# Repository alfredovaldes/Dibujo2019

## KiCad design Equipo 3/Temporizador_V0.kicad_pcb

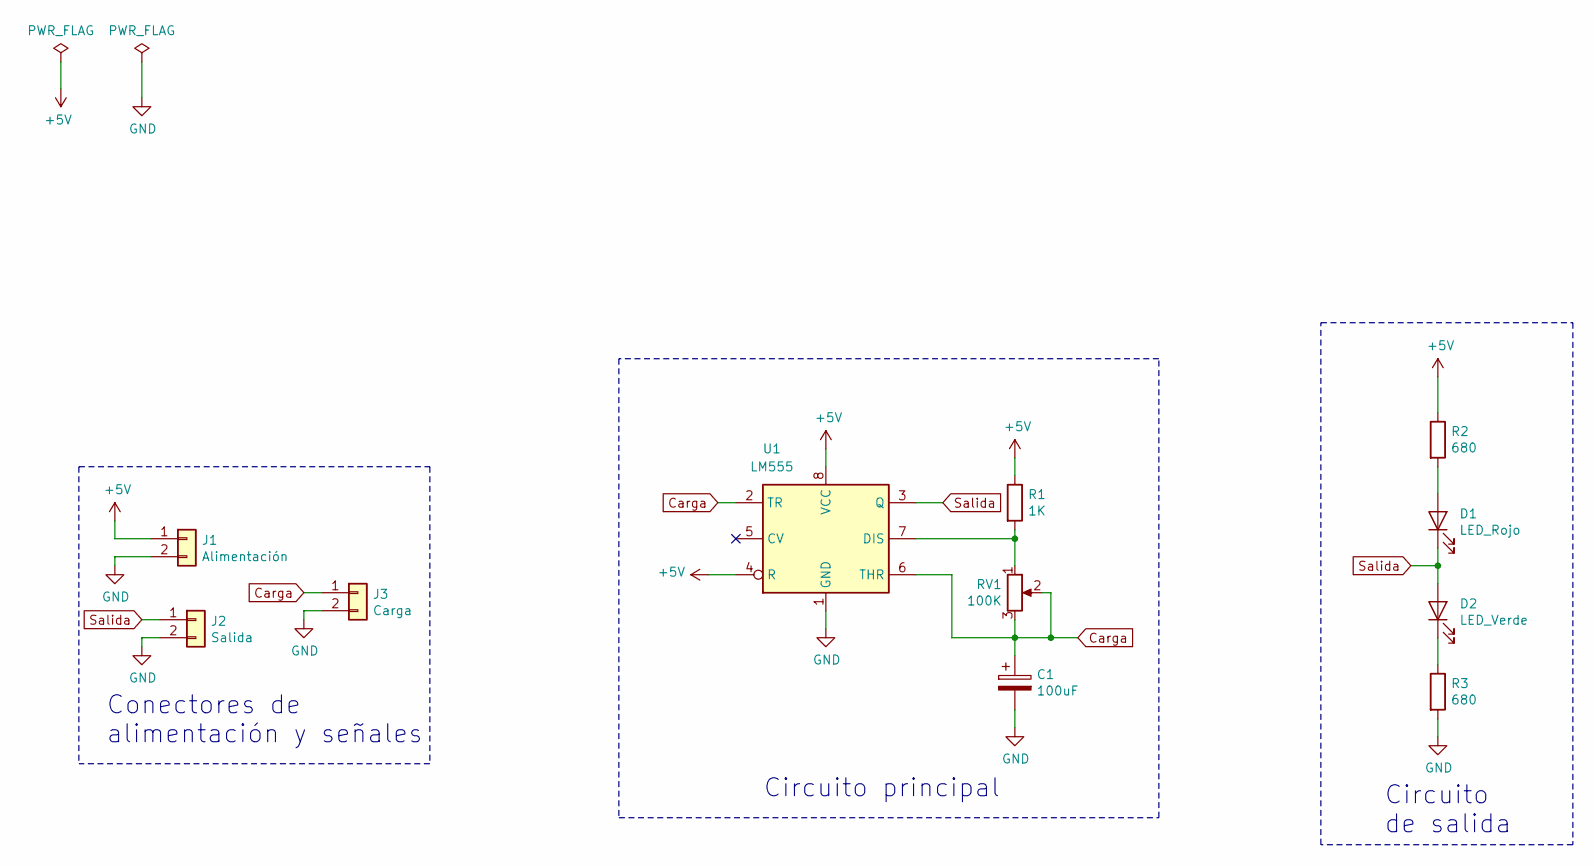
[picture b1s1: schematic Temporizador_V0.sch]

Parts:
C1: 100uF; CP_Radial_D6.3mm_P2.50mm
D1: LED_Rojo; LED_D5.0mm
D2: LED_Verde; LED_D5.0mm
J1: Alimentación; PinHeader_1x02_P2.54mm_Vertical
J2: Salida; PinHeader_1x02_P2.54mm_Vertical
J3: Carga; PinHeader_1x02_P2.54mm_Vertical
R1: 1K; R_Axial_DIN0207_L6.3mm_D2.5mm_P7.62mm_Horizontal
R2, R3: 680; R_Axial_DIN0207_L6.3mm_D2.5mm_P7.62mm_Horizontal
RV1: 100K; Potenciometro_5.08mm
U1: LM555; DIP-8_W7.62mm_Socket

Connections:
+5V: J1.1, R1.1, R2.1, U1.4 (R), U1.8 (VCC)
Carga: C1.1, J3.1, RV1.2, RV1.3, U1.2 (TR), U1.6 (THR)
GND: C1.2, J1.2, J2.2, J3.2, R3.2, U1.1 (GND)
unnamed: D1.2 (A), R2.2
unnamed: D2.1 (K), R3.1
unnamed: R1.2, RV1.1, U1.7 (DIS)
Salida: D1.1 (K), D2.2 (A), J2.1, U1.3 (Q)

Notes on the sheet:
Conectores de alimentación y señales
Circuito principal
Circuito de salida

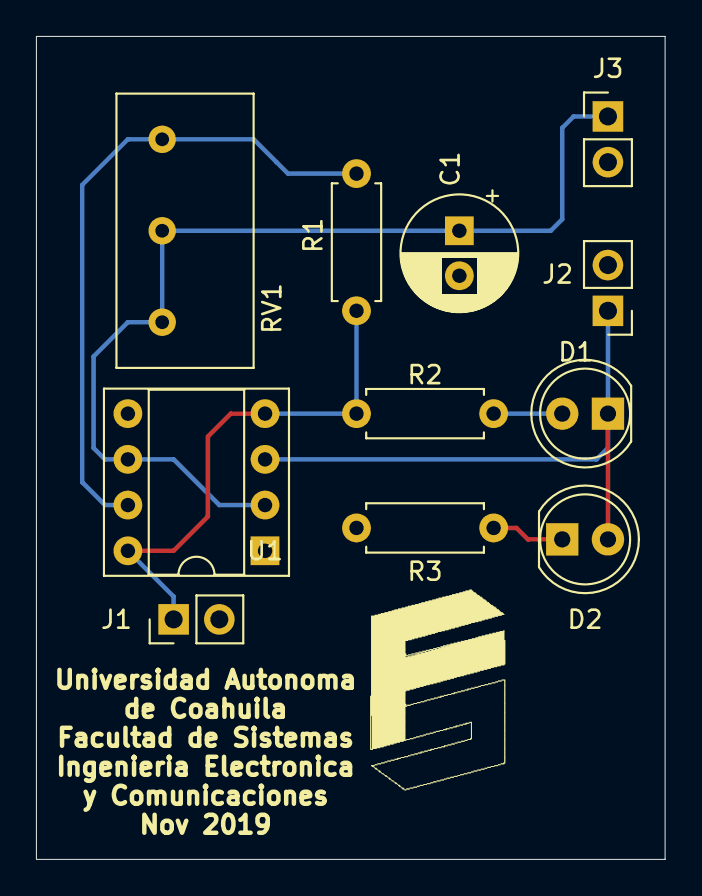
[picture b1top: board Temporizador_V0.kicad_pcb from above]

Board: 2 copper layers, 34.9 x 45.7 mm, 12 parts (0 on the bottom side), 7 nets.

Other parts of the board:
LOGO: LOGO

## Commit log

2019-12-03 Primer subida
